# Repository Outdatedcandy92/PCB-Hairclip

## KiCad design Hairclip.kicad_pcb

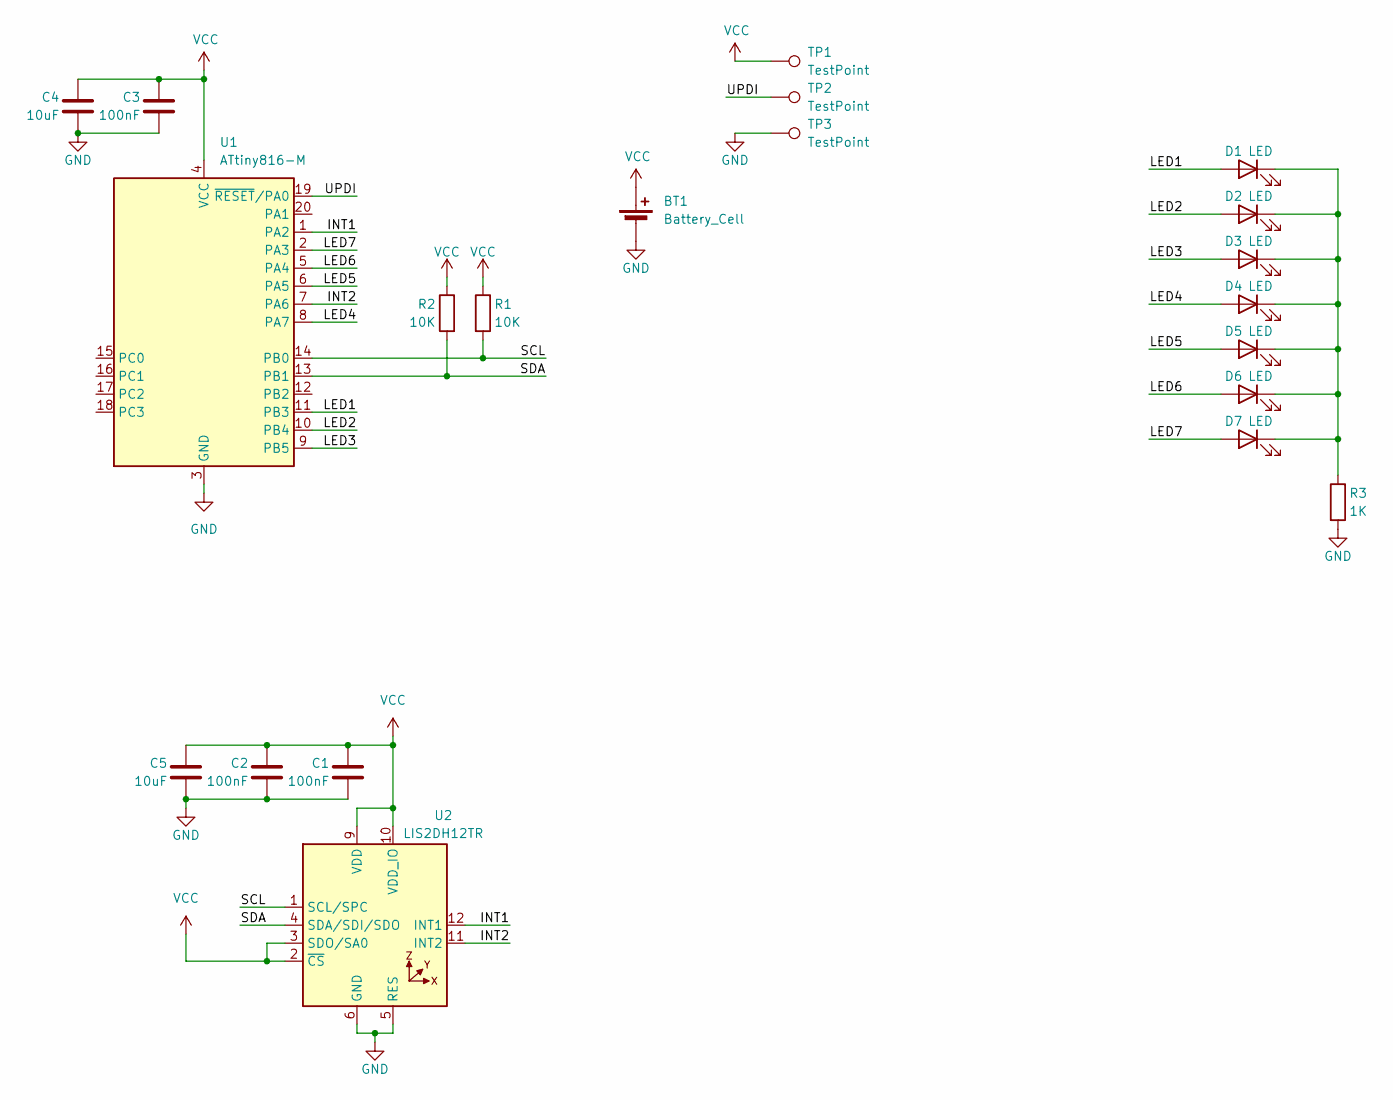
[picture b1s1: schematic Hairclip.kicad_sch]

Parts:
BT1: Battery_Cell; BAT-SMD_MY-2450-01; LCSC Part C964845
C1, C2, C3: 100nF; C_0402_1005Metric; LCSC Part C1525
C4, C5: 10uF; C_0402_1005Metric; LCSC Part C15525
D1, D2, D3, D4, D5, D6, D7: LED; LED_0402_1005Metric; LCSC Part C5875733
R1, R2: 10K; R_0402_1005Metric; LCSC Part C60490
R3: 1K; R_0402_1005Metric; LCSC Part C11702
TP1, TP2, TP3: TestPoint; TestPoint_Pad_D3.0mm
U1: ATtiny816-M; VQFN-20-1EP_3x3mm_P0.4mm_EP1.7x1.7mm; LCSC Part C2052778
U2: LIS2DH12TR; LGA-12_L2.0-W2.0-P0.50-BL; MPN LIS2DH12TR; LCSC Part C110926

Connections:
/INT1: U1.1 (PA2), U2.12 (INT1)
/INT2: U1.7 (PA6), U2.11 (INT2)
/LED1: D1.2 (A), U1.11 (PB3)
/LED2: D2.2 (A), U1.10 (PB4)
/LED3: D3.2 (A), U1.9 (PB5)
/LED4: D4.2 (A), U1.8 (PA7)
/LED5: D5.2 (A), U1.6 (PA5)
/LED6: D6.2 (A), U1.5 (PA4)
/LED7: D7.2 (A), U1.2 (PA3)
/SCL: R1.2, U1.14 (PB0), U2.1 (SCL/SPC)
/SDA: R2.2, U1.13 (PB1), U2.4 (SDA/SDI/SDO)
/UPDI: TP2.1 (1_1), U1.19 (~RESET/PA0)
GND: BT1.2 (-), C1.2, C2.2, C3.2, C4.2, C5.2, R3.2, TP3.1 (1_1), U1.3 (GND), U1.21 (GND), U2.5 (RES), U2.6 (GND), U2.7 (GND), U2.8 (GND)
unnamed: D1.1 (K), D2.1 (K), D3.1 (K), D4.1 (K), D5.1 (K), D6.1 (K), D7.1 (K), R3.1
VCC: BT1.1 (+), C1.1, C2.1, C3.1, C4.1, C5.1, R1.1, R2.1, TP1.1 (1_1), U1.4 (VCC), U2.2 (~CS), U2.3 (SDO/SA0), U2.9 (VDD), U2.10 (VDD_IO)

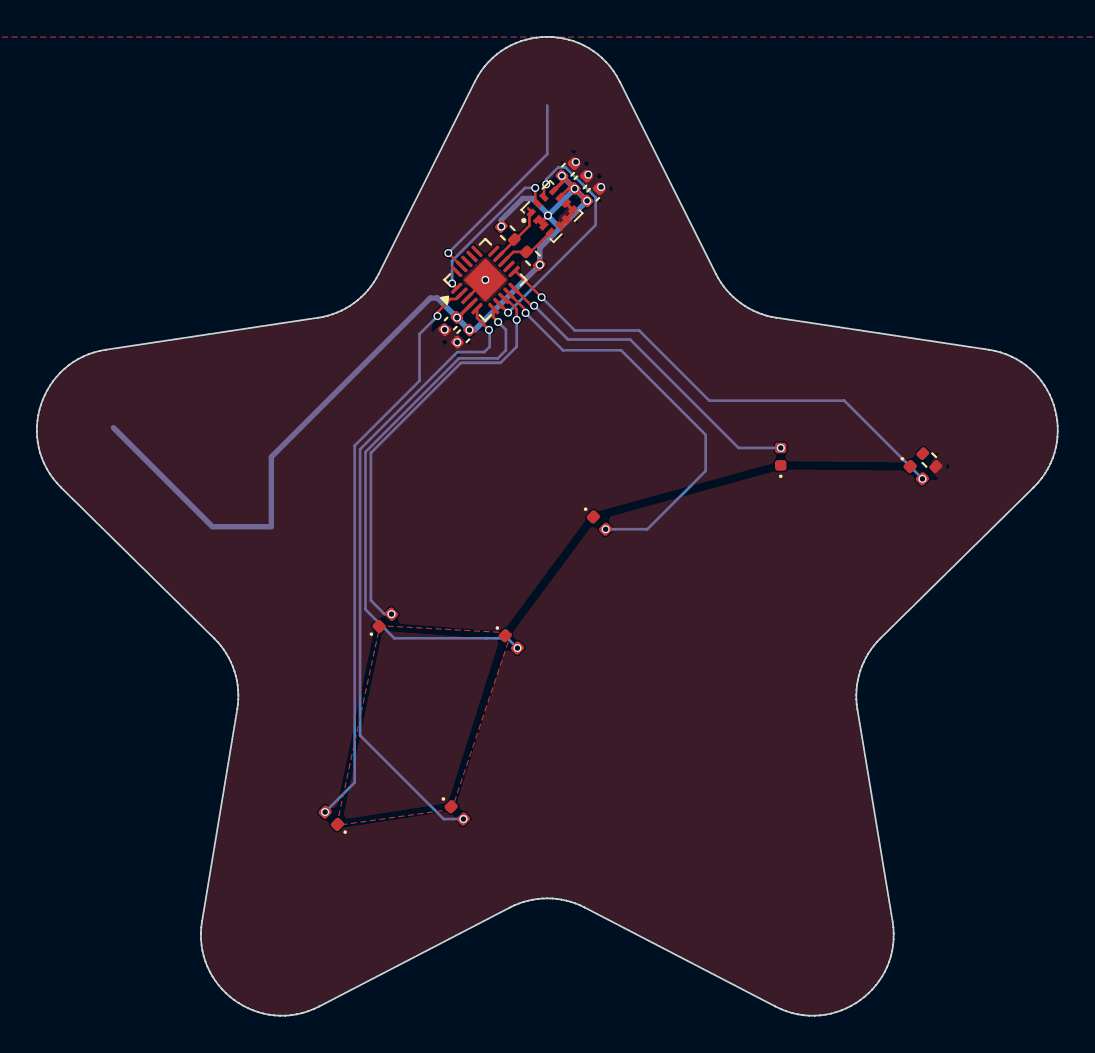
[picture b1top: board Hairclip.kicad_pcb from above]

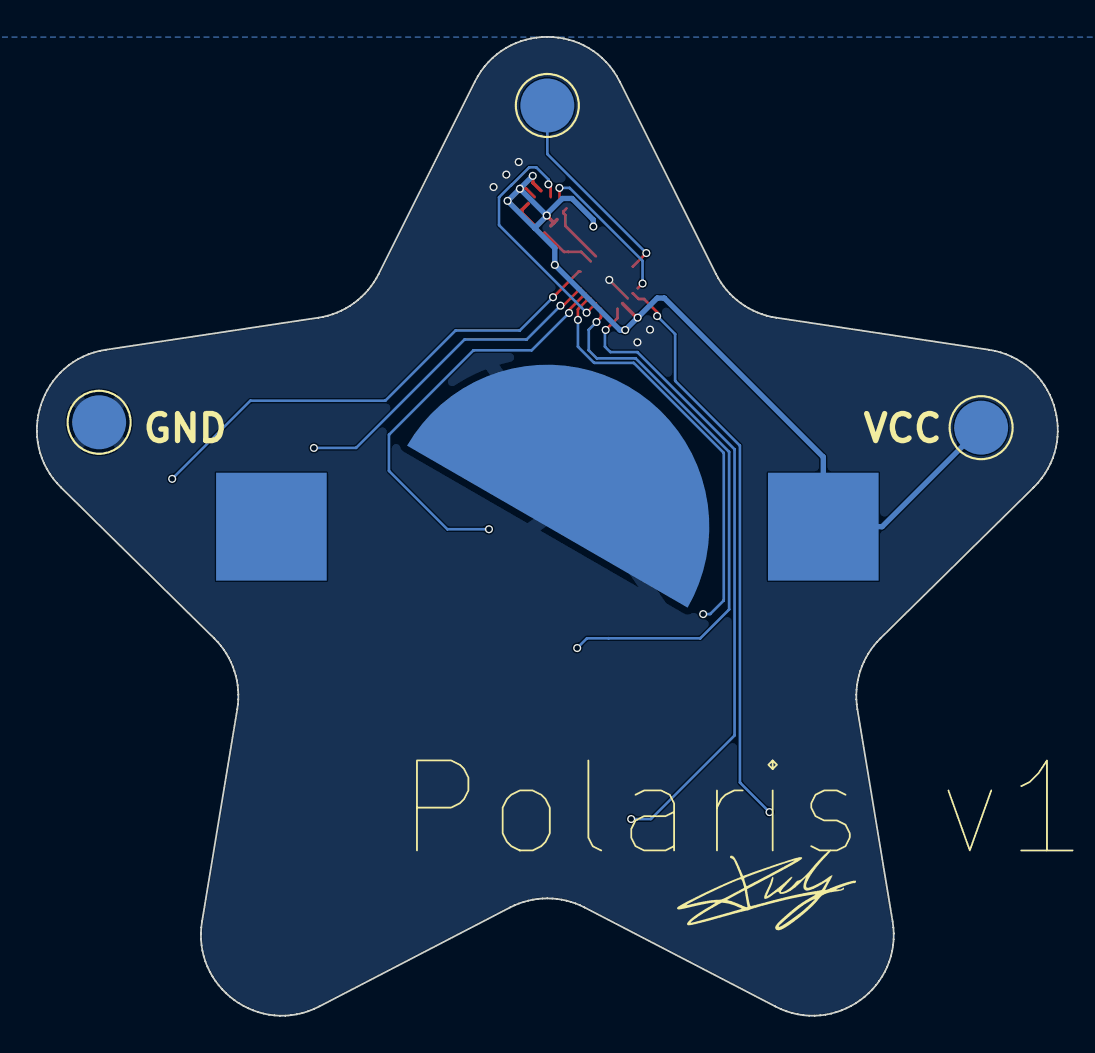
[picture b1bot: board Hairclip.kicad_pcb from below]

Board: 2 copper layers, 56.7 x 54.4 mm, 21 parts (3 on the bottom side), 15 nets.

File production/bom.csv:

Designator,Footprint,Quantity,Value,LCSC Part #
BT1,BAT-SMD_MY-2450-01,1,Battery_Cell,C964845
"C1, C2, C3",0402,3,100nF,
"C4, C5",0402,2,10uF,
"D1, D2, D3, D4, D5, D6, D7",0402,7,LED,
"R1, R2",0402,2,10K,
R3,0402,1,1K,
"TP1, TP2, TP3",TestPoint_Pad_D3.0mm,3,TestPoint,
U1,VQFN-20-1EP_3x3mm_P0.4mm_EP1.7x1.7mm,1,ATtiny816-M,
U2,LGA-12_L2.0-W2.0-P0.50-BL,1,LIS2DH12TR,C110926
